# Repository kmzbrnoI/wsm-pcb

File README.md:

# WSM-PCB: A Wireless SpeedoMeter PCB

WSM is a model railroad car which measures speed of a train and transmits it via
Bluetooth. This repository contains schematics & PCBs layout for all the PCBs
used in the car.

The whole car is designed to be supplied by any 3.7V LiPo battery. PCB design
allows you to charge the battery via USB, so no disconnecting of the battery
nor external changer is required. The measurement is based on an opto-sensor
capturing a perforated wheel connected to an axis of a wheel of the car. The
speed-data are transmitted via HC-05 bluetooth module to any device supporting
SPP bluetooth profile.

This solution consists of a main board (`main-board.{brd,sch}`) and board
for connecting the optosensor (`opto-con.{brd,sch}`). Main board contains all
the logic, optosensor connector board contains no logic, it serves only for
mechanical purposes. Optosensor connector board is not required.

## Features

 * Speed-measuring based on opto-sensor.
 * Size 50×18 mm.
 * Transmits data via bluetooth.
 * No external power supply is required (no current from tracks).
 * Runs on battery, can measure up to 8 hours based on chosen battery.
 * Integrated charging circuit.
 * Charging from micro-USB connector.
 * ON/OFF switch.
 * Measuring of a battery level & undervoltage protection.

## Resources

 * [Firmware to the main CPU](https://github.com/kmzbrnoI/wsm-fw).
 * [Software to PC](https://github.com/kmzbrnoI/wsm-speed-reader).

## Toolkit

This PCB was designed in Eagle 9.

## Sensor

This boards was tested with
[GP1S23 opto sensor](http://static6.arrow.com/aropdfconversion/33ee6367e3f24c1538ff4b63e7c9272b758d9d51/tec_datasheet_gp1s23.pdf).
This sensor in commonly available at KY-010 Arduino module.

## Mechanics

## `place.tex`

This TeX file allows you to merge top and bottom place layouts into a single
document.

## Authors

 * Jan Horacek ([jan.horacek@kmz-brno.cz](mailto:jan.horacek@kmz-brno.cz))

## Credits

 * This project is inspired by the measure car designed by *Petr Travnik*.
 * The ON-OFF switch part is inspired by the RB3201 project of *[RoboticsBrno
   ](https://github.com/RoboticsBrno)*.
 * Many thanks to *Michal Petrilak* for help with development of this project.

## License

This project is released under the [Creative Commons Attribution-ShareAlike 4.0
](https://creativecommons.org/licenses/by-sa/4.0) license.

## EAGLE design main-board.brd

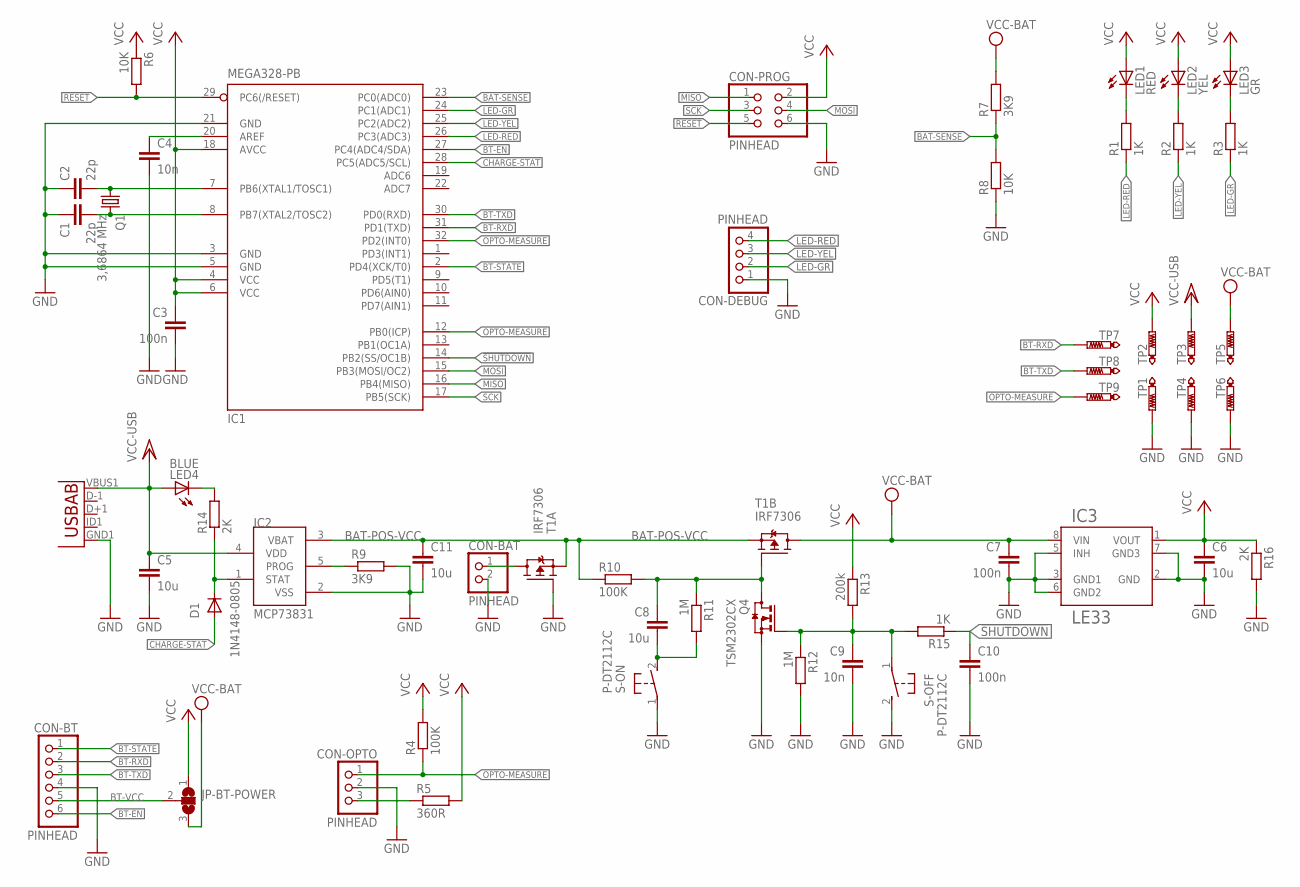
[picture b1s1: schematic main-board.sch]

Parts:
C1, C2: 22p; C0805
C3, C7, C10: 100n; C0805
C4, C9: 10n; C0805
C5, C6, C8, C11: 10u; C0805
CON-BAT: PINHEAD; 1X02
CON-BT: PINHEAD; 1X06
CON-DEBUG: PINHEAD; 1X04
CON-OPTO: PINHEAD; 1X03
CON-PROG: PINHEAD; 2X03
D1: 1N4148-0805; R0805
IC1: MEGA328-PB; TQFP32-08
IC2: MCP73831; SOT23-5L
IC3: LE33; SO08
JP-BT-POWER: SJ2W; SJ_2
LED1: RED; CHIP-LED0805
LED2: YEL; CHIP-LED0805
LED3: GR; CHIP-LED0805
LED4: BLUE; CHIP-LED0805
Q1: 3,6864 MHz; HC49UP
Q4: TSM2302CX; SOT23
R1, R2, R3, R15: 1K; R0805
R4, R10: 100K; R0805
R5: 360R; R0805
R6, R8: 10K; R0805
R7, R9: 3K9; R0805
R11, R12: 1M; R0805
R13: 200k; R0805
R14, R16: 2K; R0805
S-OFF: P-DT2112C; DTSM-3
S-ON: P-DT2112C; DTSM-3
T1: IRF7306; SO08-IRF
TP1, TP2, TP3, TP4, TP5, TP6, TP7, TP8, TP9: PTR1B1,27; B1,27
U1: USB""; USB-MICRO-SMD

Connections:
!RESET: CON-PROG.5, IC1.29 (PC6(/RESET)), R6.2
!SHUTDOWN: C10.1, IC1.14 (PB2(SS/OC1B)), R15.1
!SHUTDOWN_INT: C9.1, Q4.1 (G), R12.1, R13.2, R15.2, S-OFF.1
BAT-POS-VCC: C11.1, IC2.3 (VBAT), R10.1, T1.1 (S), T1.3 (S)
BAT-RAW-VCC: CON-BAT.1, T1.7 (D), T1.8 (D)
BAT-SENSE: IC1.23 (PC0(ADC0)), R7.1, R8.2
BT-EN: CON-BT.6, IC1.27 (PC4(ADC4/SDA))
BT-RXD: CON-BT.2, IC1.31 (PD1(TXD)), TP7.PP
BT-STATE: CON-BT.1, IC1.2 (PD4(XCK/T0))
BT-TXD: CON-BT.3, IC1.30 (PD0(RXD)), TP8.PP
BT-VCC: CON-BT.5, JP-BT-POWER.2
CHARGE-PROG: IC2.5 (PROG), R9.1
CHARGE-STAT: D1.A, IC1.28 (PC5(ADC5/SCL))
CHARGE-STAT-INT: D1.K (C), IC2.1 (STAT), R14.1
CHARGE-STAT-LED: LED4.C, R14.2
CPU-REF: C4.1, IC1.20 (AREF)
CR1: C1.2, IC1.8 (PB7(XTAL2/TOSC2)), Q1.2
CR2: C2.2, IC1.7 (PB6(XTAL1/TOSC1)), Q1.1
GND: C1.1, C2.1, C3.2, C4.2, C5.2, C6.2, C7.2, C9.2, C10.2, C11.2, CON-BAT.2, CON-BT.4, CON-DEBUG.1, CON-OPTO.2, CON-PROG.6, IC1.3 (GND), IC1.5 (GND), IC1.21 (GND), IC2.2 (VSS), IC3.2 (GND), IC3.3 (GND1), IC3.5 (INH), IC3.6 (GND2), IC3.7 (GND3), Q4.2 (S), R8.1, R9.2, R12.2, R16.2, S-OFF.2, S-ON.1, T1.2 (G), TP1.PP, TP4.PP, TP6.PP, U1.GND1 (GND)
LED-GR: CON-DEBUG.2, IC1.24 (PC1(ADC1)), R3.1
LED-GR-R: LED3.C, R3.2
LED-RED: CON-DEBUG.4, IC1.26 (PC3(ADC3)), R1.1
LED-RED-R: LED1.C, R1.2
LED-YEL: CON-DEBUG.3, IC1.25 (PC2(ADC2)), R2.1
LED-YEL-R: LED2.C, R2.2
MISO: CON-PROG.1, IC1.16 (PB4(MISO))
MOSI: CON-PROG.4, IC1.15 (PB3(MOSI/OC2))
OPTO-MEASURE: CON-OPTO.1, IC1.12 (PB0(ICP)), IC1.32 (PD2(INT0)), R4.1, TP9.PP
OPTO-VCC: CON-OPTO.3, R5.1
SCK: CON-PROG.3, IC1.17 (PB5(SCK))
START_BUTTON: C8.2, R11.2, S-ON.2
START_GATE: C8.1, Q4.3 (D), R10.2, R11.1, T1.4 (G)
VCC: C3.1, C6.1, CON-PROG.2, IC1.4 (VCC), IC1.6 (VCC), IC1.18 (AVCC), IC3.1 (VOUT), JP-BT-POWER.1, LED1.A, LED2.A, LED3.A, R4.2, R5.2, R6.1, R13.1, R16.1, TP2.PP
VCC-BAT: C7.1, IC3.8 (VIN), JP-BT-POWER.3, R7.2, T1.5 (D), T1.6 (D), TP5.PP
VCC-USB: C5.1, IC2.4 (VDD), LED4.A, TP3.PP, U1.VBUS1 (VBUS)

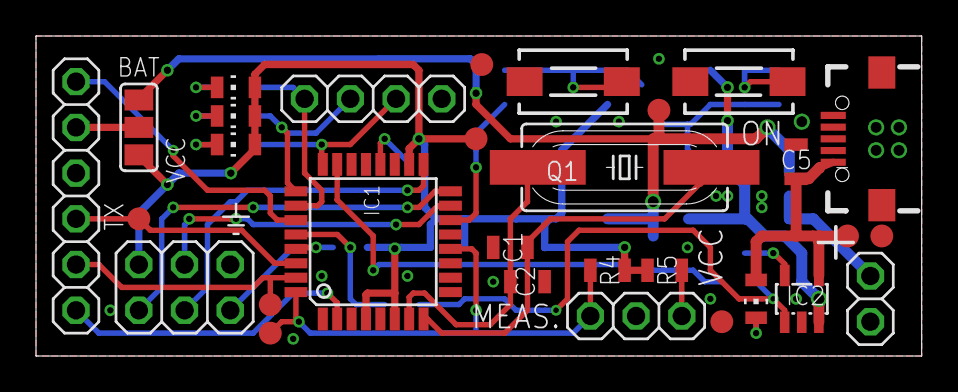
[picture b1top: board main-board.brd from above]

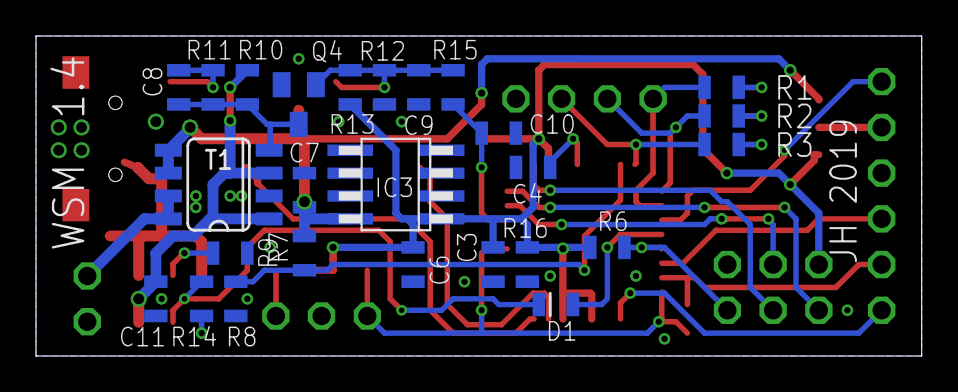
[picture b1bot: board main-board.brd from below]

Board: 2 copper layers, 49.2 x 17.8 mm, 56 parts (26 on the bottom side), 35 nets.

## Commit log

2018-07-11 Initial commit.
2018-07-11 Add first parts of schematics.
2018-07-11 Another improvements.
2018-07-12 Add LE33 LDO.
2018-07-12 Add power control of peripherals.
2018-07-12 Add power jumper.
2018-07-12 Add LED to charging circuit.
2018-07-13 Eagle 9.0 & on & off buttons.
2018-07-13 Reset -> !reset.
2018-07-13 Fix unconnected LEDS.
2018-07-13 Add connector for debug measuring.
2018-07-13 Decrease current to !SHUTDOWN to 10 mA.
2018-07-13 Add polarity protection.
2018-07-13 Add missing wires & edit debug connector.
2018-07-13 Add names to signals.
2018-07-13 Unify names of resistors & capacitors.
2018-07-14 Faster on & off switches.
2018-07-14 Add net classes.
2018-07-14 Remove unwanted VCC/2.
2018-07-14 Board: initial commit.
2018-07-14 First prototype of PCB.
2018-07-14 Board: pads, minor improvements.
2018-07-14 Board: center pinheaders.
2018-07-14 Board: add texts for silkscreen.
2018-07-14 Version 1.1.
2018-07-14 Add optoconnector PCB.
2018-07-15 Move some wires to make schematics more clear.
2018-07-15 BT takes power from VCC-BAT, not BAT-POS-VCC.
2018-07-15 Add min. drill size to net classes.
2018-07-15 Change shape of pins on pinheaders.
2018-07-15 Rename main board.
2018-07-15 Add README.
2018-07-15 Fix typo.
2018-07-15 Add note about resources.
2018-07-16 Optimize for BOM.
2018-07-19 Con-bt-power -> jumper BT power.
2018-07-19 Connect OPTO-MEASURE to ICP (PB0).
2018-07-19 Move CHARGE-STAT to digital pin.
2018-07-19 Schematics: move power parts together.
2018-07-19 Fix polarity-protection MOSFET.
2018-07-20 Add diode to CHARGE-STAT pin.
2018-07-21 Change value of C9.
2018-07-22 Use SJ2W for BT power switching.
2018-07-22 Add 'basic' & 'debug' assembly variants.
2018-07-30 Update drill in micro-USB connector.
2018-07-30 Edit names for silkscreen.
2018-07-30 Update active layers to default.
2018-08-14 Create nice place views.
2018-08-14 Add place generator script.
2018-08-18 Fix shutdown circuit.
    Shutting down from CPU should work now.
2018-08-18 Change voltage divisor (use LDO as reference).
2018-08-28 4K -> 3K9.
2018-08-29 Add silkscreen for PCB manufacturing.
2018-08-29 Update values of resistors.
2018-08-29 Fix placing.
2018-08-29 Show default layers.
2018-09-20 Write meaning of measure signals to silkscreen.
2018-09-20 Add proper LICENSE.
2018-09-20 Add all information to README.
2018-12-30 Set R4 to 100k.
    The construction of second protoype showed that the value of the pull-up
    is critical for proper device function.
2019-01-05 v1.4.
2019-01-18 Protect charging circuit against polarity change too.
2019-01-18 Decrease mdCopperDimension to 10 mil.
2019-01-18 Remove wire stubs, make LED's pads smaller.
2019-01-18 Adjuct place a little.
